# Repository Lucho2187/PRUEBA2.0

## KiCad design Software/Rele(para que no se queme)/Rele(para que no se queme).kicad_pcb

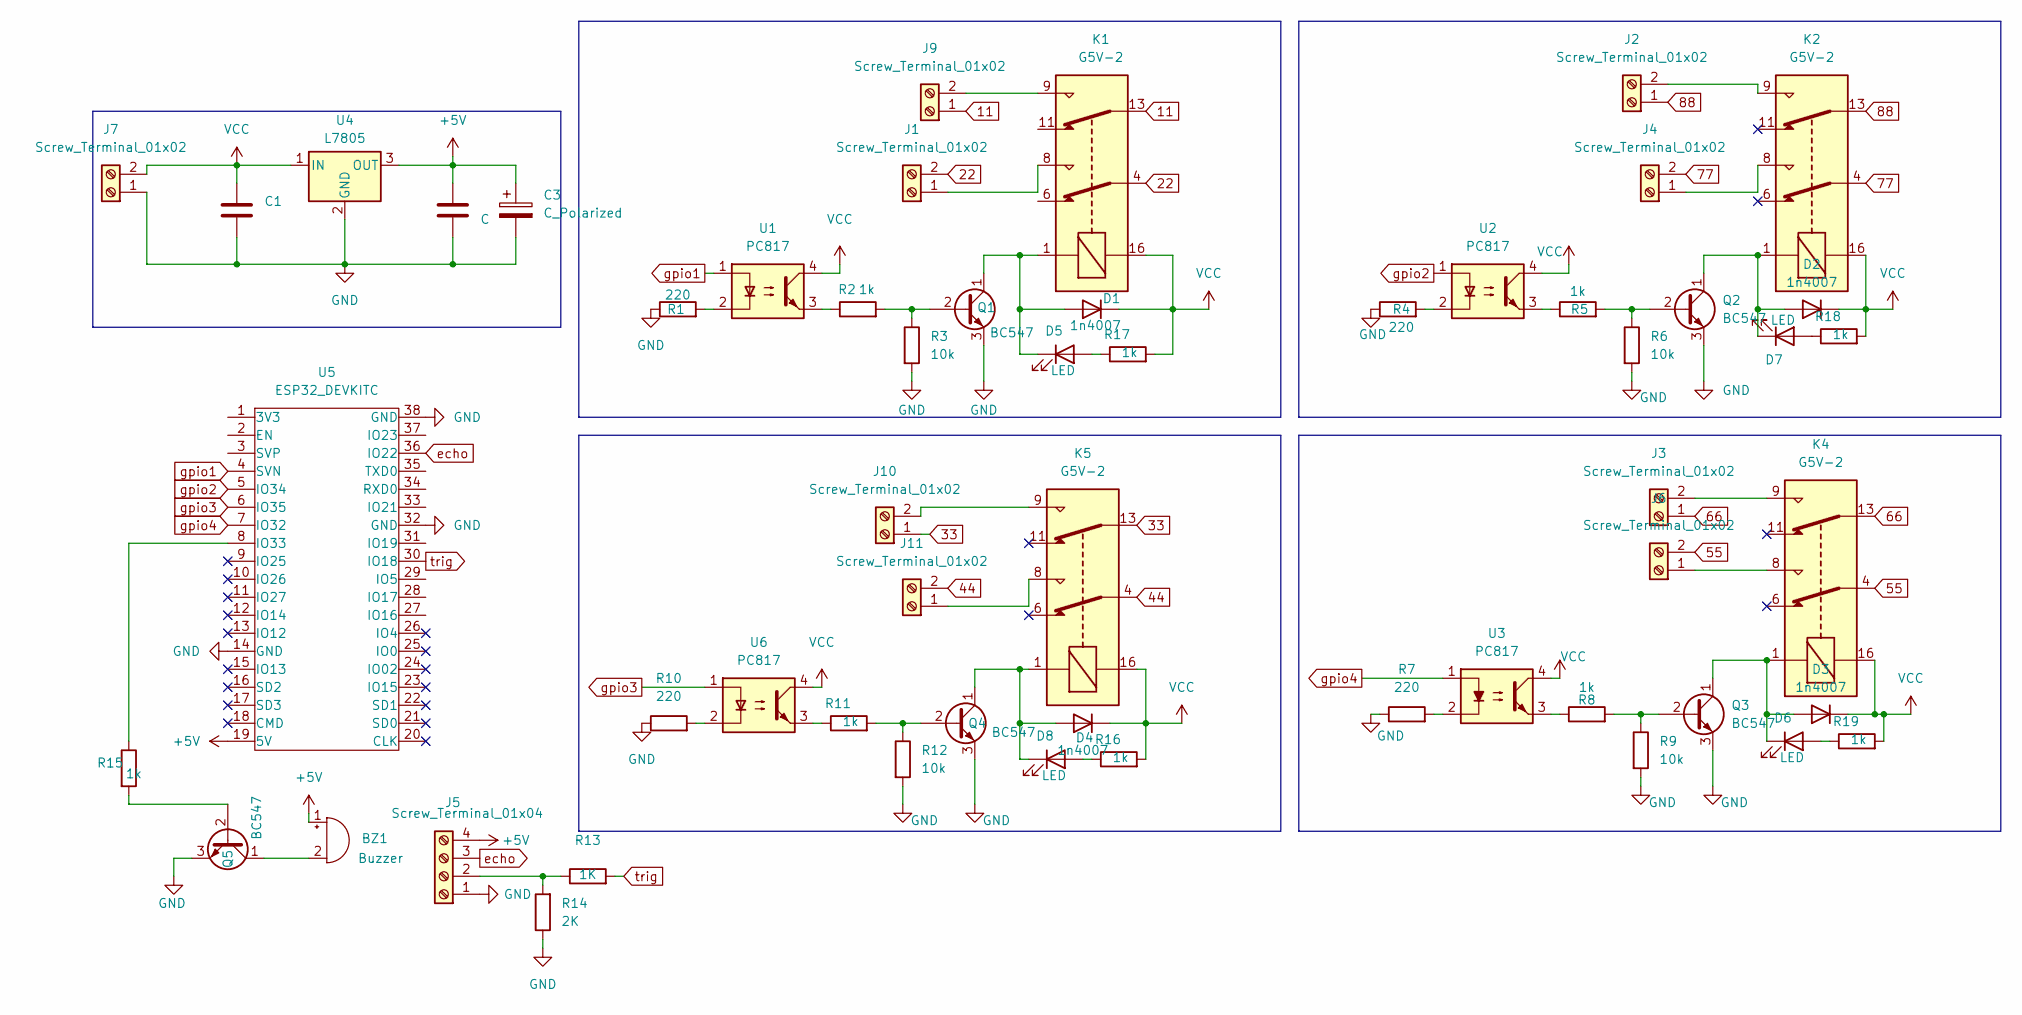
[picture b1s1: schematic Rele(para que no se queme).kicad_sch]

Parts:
BZ1: Buzzer; Pin_Header_2
C1, C2: C; C_0805_2012Metric_Pad1.18x1.45mm_HandSolder
C3: C_Polarized; C_Radial_D6.3mm_H5.0mm_P2.50mm
D1, D2, D3, D4: 1n4007; D_SMA
D5, D6, D7, D8: LED; LED_PLCC-2_3.4x3.0mm_AK
J1, J2, J3, J4, J6, J9, J10, J11: Screw_Terminal_01x02; TerminalBlock_Altech_AK300-2_P5.00mm
J5: Screw_Terminal_01x04; pin_strip_4
J7: Screw_Terminal_01x02; BORNERA2
K1, K2, K4, K5: G5V-2; Relay_DPDT_Omron_G5V-2
Q1, Q2, Q3, Q4: BC547; TO-92_Inline_Wide
Q5: BC547; SOT-23
R1, R4, R7, R10: 220; R_0805_2012Metric_Pad1.20x1.40mm_HandSolder
R2, R5, R8, R11, R15, R16, R17, R18, R19: 1k; R_0805_2012Metric_Pad1.20x1.40mm_HandSolder
R3, R6, R9, R12: 10k; R_0805_2012Metric_Pad1.20x1.40mm_HandSolder
R13: 1K; R_0805_2012Metric_Pad1.20x1.40mm_HandSolder
R14: 2K; R_0805_2012Metric_Pad1.20x1.40mm_HandSolder
U1, U3, U6: PC817; DIP-4_PC817
U2: PC817; DIP-4_W7.62mm
U4: L7805; TO-263-3_TabPin2
U5: ESP32_DEVKITC; ESP32S

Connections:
11: J9.1, K1.13
22: J1.2, K1.4
33: J10.1, K5.13
44: J11.2, K5.4
55: J6.2, K4.4
66: J3.1, K4.13
77: J4.2, K2.4
88: J2.1, K2.13
+5V: BZ1.1 (+), C2.1, C3.1, J5.4, U4.3 (OUT), U5.19 (5V)
GND: C1.2, C2.2, C3.2, J5.1, J7.1, Q1.3 (E), Q2.3 (E), Q3.3 (E), Q4.3 (E), Q5.3 (E), R1.1, R3.2, R4.1, R6.2, R7.1, R9.2, R10.1, R12.2, R14.1, U4.2 (GND), U5.14 (GND), U5.32 (GND), U5.38 (GND)
unnamed: BZ1.2 (-), Q5.1 (C)
unnamed: D1.2 (A), D5.1 (K), K1.1, Q1.1 (C)
unnamed: D2.2 (A), D7.1 (K), K2.1, Q2.1 (C)
unnamed: D3.2 (A), D6.1 (K), K4.1, Q3.1 (C)
unnamed: D4.2 (A), D8.1 (K), K5.1, Q4.1 (C)
unnamed: D5.2 (A), R17.1
unnamed: D6.2 (A), R19.1
unnamed: D7.2 (A), R18.1
unnamed: D8.2 (A), R16.1
unnamed: J1.1, K1.8
unnamed: J2.2, K2.9
unnamed: J3.2, K4.9
unnamed: J4.1, K2.8
unnamed: J5.2, R13.1, R14.2
unnamed: J6.1, K4.8
unnamed: J9.2, K1.9
unnamed: J10.2, K5.9
unnamed: J11.1, K5.8
unnamed: Q1.2 (B), R2.2, R3.1
unnamed: Q2.2 (B), R5.2, R6.1
unnamed: Q3.2 (B), R8.2, R9.1
unnamed: Q4.2 (B), R11.2, R12.1
unnamed: Q5.2 (B), R15.2
unnamed: R1.2, U1.2
unnamed: R2.1, U1.3
unnamed: R4.2, U2.2
unnamed: R5.1, U2.3
unnamed: R7.2, U3.2
unnamed: R8.1, U3.3
unnamed: R10.2, U6.2
unnamed: R11.1, U6.3
unnamed: R15.1, U5.8 (IO33)
VCC: C1.1, D1.1 (K), D2.1 (K), D3.1 (K), D4.1 (K), J7.2, K1.16, K2.16, K4.16, K5.16, R16.2, R17.2, R18.2, R19.2, U1.4, U2.4, U3.4, U4.1 (IN), U6.4
echo: J5.3, U5.36 (IO22)
gpio1: U1.1, U5.4 (SVN)
gpio2: U2.1, U5.5 (IO34)
gpio3: U5.6 (IO35), U6.1
gpio4: U3.1, U5.7 (IO32)
trig: R13.2, U5.30 (IO18)

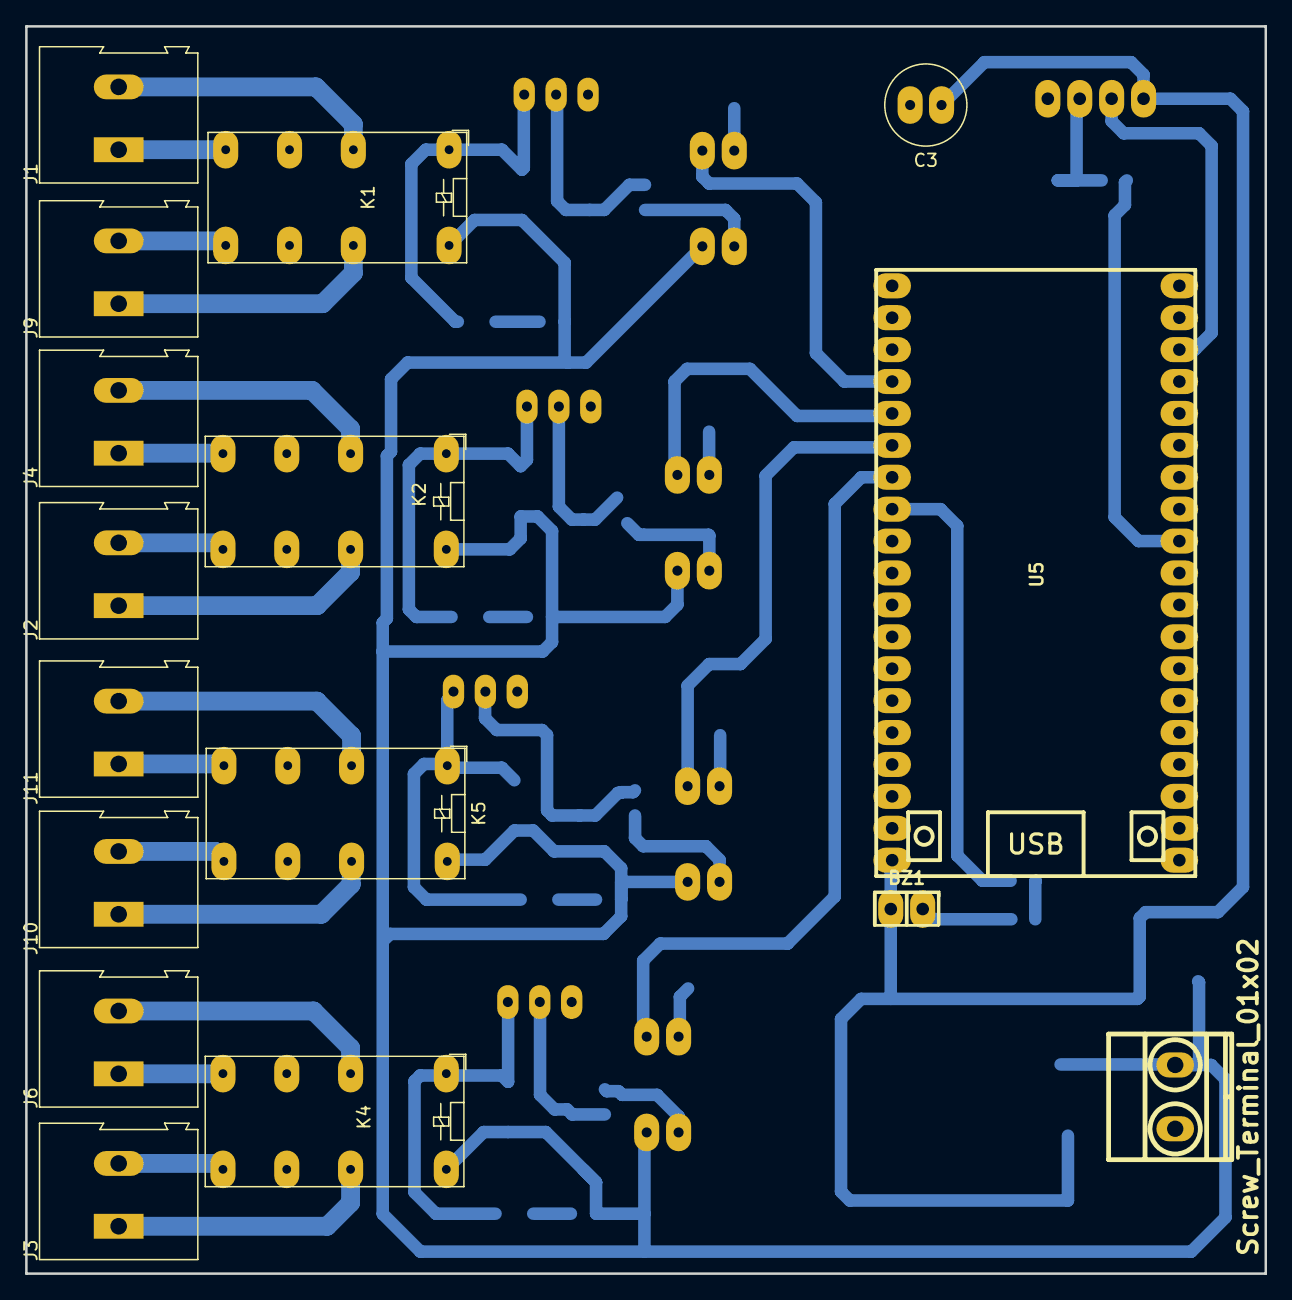
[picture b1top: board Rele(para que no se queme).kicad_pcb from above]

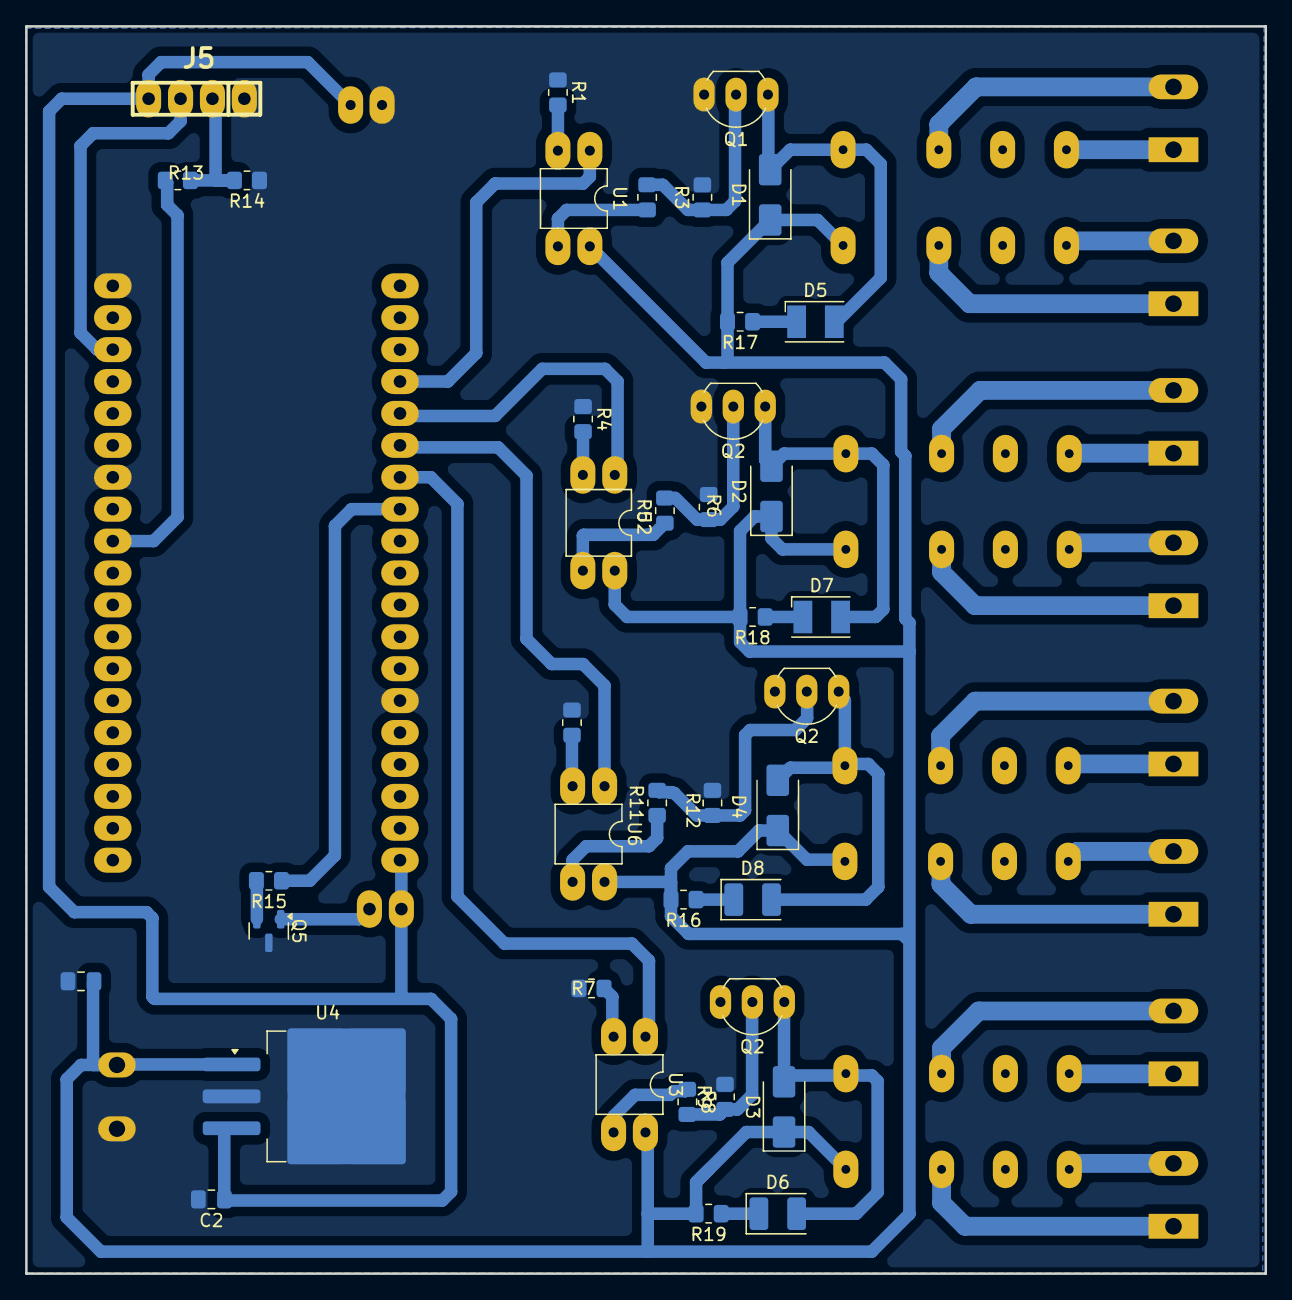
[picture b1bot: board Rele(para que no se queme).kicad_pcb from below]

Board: 2 copper layers, 98.7 x 99.3 mm, 56 parts (40 on the bottom side), 49 nets.

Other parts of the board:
Q2#2, Q2#3: BC547; TO-92_Inline_Wide

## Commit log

2025-04-14 agregue el index.html
2025-07-02 2do commit
2025-07-11 3er commit
